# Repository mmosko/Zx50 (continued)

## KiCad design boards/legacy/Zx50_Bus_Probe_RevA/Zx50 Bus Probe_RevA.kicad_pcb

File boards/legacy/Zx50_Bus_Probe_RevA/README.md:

# Zx50 Bus Probe & Injector Card - Hardware Reference

*Note: For details on the firmware (PIC18F4620 and Pi Pico) and the automated laptop testing scripts, please refer to the separate software documentation: [Zx50BusProbeSw.md](../../Zx50_BusProbe_Firmware/Zx50BusProbeSw.md).*

## 1. Overview and Purpose
The Zx50 Bus Probe is a hybrid diagnostic tool designed specifically for a Z80-based Zx50 backplane architecture. It serves as an active oscilloscope probe, an arbitrary signal injector, and a digital logic analyzer tap. 

Instead of manually moving oscilloscope probes across an active backplane, the Zx50 Probe allows a user to digitally route any of the 72 backplane signals to a central BNC output, inject external signals via a BNC input, and monitor system health via an onboard UI.

There is a Receiver card that attaches to the Zx50 bus. It has a Pi PICO as the interface to a host computer. The Pico orchestrates the backplane signal multiplexing. It is attached via SPI to an 18F4620 PIC that has two GPIO expanders. The PIC is the Zx50 bus debugger. It can read or write to the bus and it can control the clocks. 

There is a Sender card that attaches to the Receiver via 2x5 ribbon cable. The Sender card attaches to an AFG to put signals on backplane traces. These can be monitored by the Receiver. Both sender and receiver have high-speed op amps and BNC connectors to attach to lab equipment.

## 2. The Universal Board Architecture
To minimize fabrication costs and guarantee matched signal paths, the system is designed as a **Universal PCB**. A single board design can be populated differently to serve as either the "Receiver" (The Brain) or the "Sender" (The Drone).

* **The Receiver (Master):** Populated with a Raspberry Pi Pico (RP2040) and a PIC18F4620. It orchestrates the signal routing, generates hardware-level system clocks, handles high-speed Z80 interrupts (`~WAIT~`, `~INT~`), and hosts the physical User Interface.
* **The Sender (Slave):** The Pi Pico and PIC are left unpopulated. It relies on the Receiver to command its local analog matrix via a 10-pin right-angle IDC ribbon cable.
* **The Jumper Matrix (3x7 Block):** A physical 21-pin routing block determines the board's role by directing the 5V control signals:
  * **Position 1-2 (Receiver Mode):** The onboard Pico drives both the local analog matrix and the remote Sender board via the ribbon cable.
  * **Position 2-3 (Sender Mode / Mirror Mode):** The local analog matrix is driven by external signals arriving from the ribbon cable.

## 3. Core Subsystems

### A. The "Voltage Firewall" (Level Shifting)
The Pi Pico operates strictly at 3.3V, while the Zx50 backplane and logic operate at 5.0V. 
* A **`74AHCT541`** buffer acts as a unidirectional level shifter and line driver.
* The "T" (TTL-compatible) inputs interpret the Pico's 3.3V signals as a valid logic HIGH, stepping them up to a robust 5.0V to drive the local multiplexers and safely push signals down the ribbon cable to the Sender board.

### B. The Analog Matrix
The core of the probing capability is a massive 72-channel crosspoint matrix.
* **Multiplexers:** Nine `CD74HC4051E` 8-channel analog multiplexers (High-Speed CMOS variant chosen over legacy `CD4051BE` to ensure <70Ω $R_{ON}$ and >100MHz bandwidth for sharp Z80 square waves).
* **Decoding:** A 4-to-16 line decoder (`74HC154` or cascaded `74HC138`s) manages the Chip Select lines for the multiplexers. Sending address `1111` (15) targets a "Phantom Mux," safely disabling the entire matrix to isolate the test equipment from the bus.
* **Op-Amps:** High-speed `OPA356xxD` CMOS operational amplifiers buffer the analog signals immediately before the `IN` and `OUT` BNC jacks to prevent the oscilloscope or function generator from loading the backplane.

### C. The Dedicated Logic Analyzer Field
To support professional diagnostic equipment (e.g., Tektronix logic analyzers), the rear of the card features a raw, unbuffered test point field.
* Arranged in standard 2xN 2.54mm pitch groupings spaced out by function: `ADDR [0:15]`, `DATA [0:7]`, `CTRL [0:7]`, `SHADOW_DATA [0:7]`, `SHADOW_CTRL [0:7]`, and `CLOCK [0:1]`.
* **Dedicated Ground Row:** Every signal pin is paired directly with an adjacent `GND` pin (Row 2), ensuring short return paths and pristine signal integrity for flying-lead probes.
* The headers are intentionally unbuffered, relying on the <2pF capacitance of professional logic analyzer pods to spy on the true analog state of the bus.

## 4. Mechanical & Physical Design

* **Asymmetric "Tower" Form Factor:** The PCB utilizes an inverted-T (or L-shaped) `Edge.Cuts` profile. The base fits the standard 5-inch Zx50 card dimensions, while the front UI section extends upward to 7 inches. This ensures the display and status LEDs clear the adjacent memory/CPU cards in the chassis.
* **User Interface:**
  * **Primary Display:** An `EA DIP205-4` 20x4 Character LCD, mounted flush to the PCB. It runs natively on the Pico's 3.3V SPI bus, with a dedicated 33Ω resistor dropping the 5V rail for the yellow/green backlight.
  * **Status LEDs:** Three right-angle horizontal LEDs (`CLK`, `MCLK`, `PWR`) mounted on the top edge of the board to provide immediate, bench-visible heartbeat and clock status.
* **Horizontal Interconnects:** The PIC ICSP programming header (`J4`) and the Sender/Receiver ribbon cable header (`J8`) use right-angle footprints to prevent cable collisions with adjacent Zx50 cards.

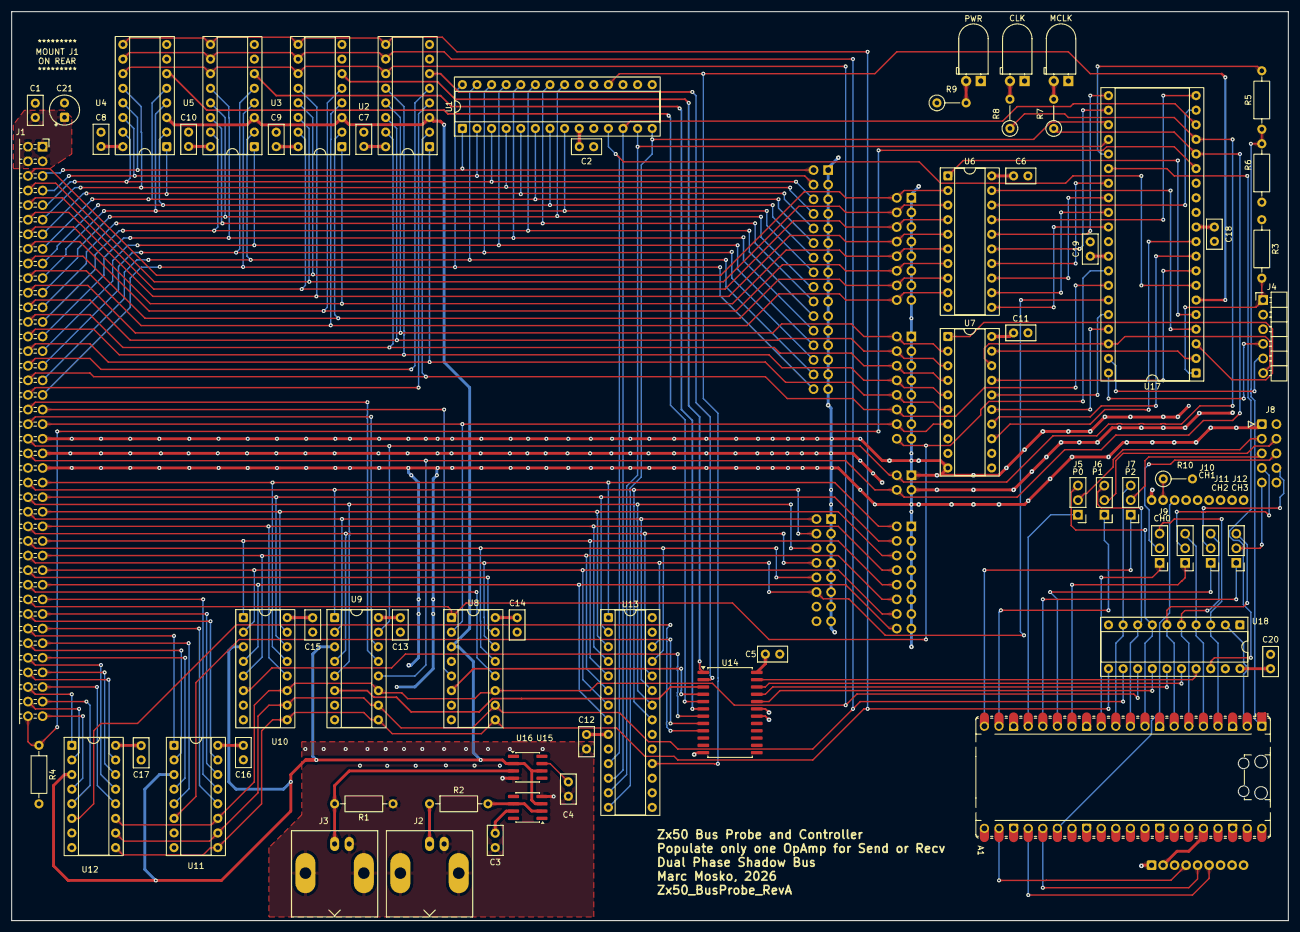
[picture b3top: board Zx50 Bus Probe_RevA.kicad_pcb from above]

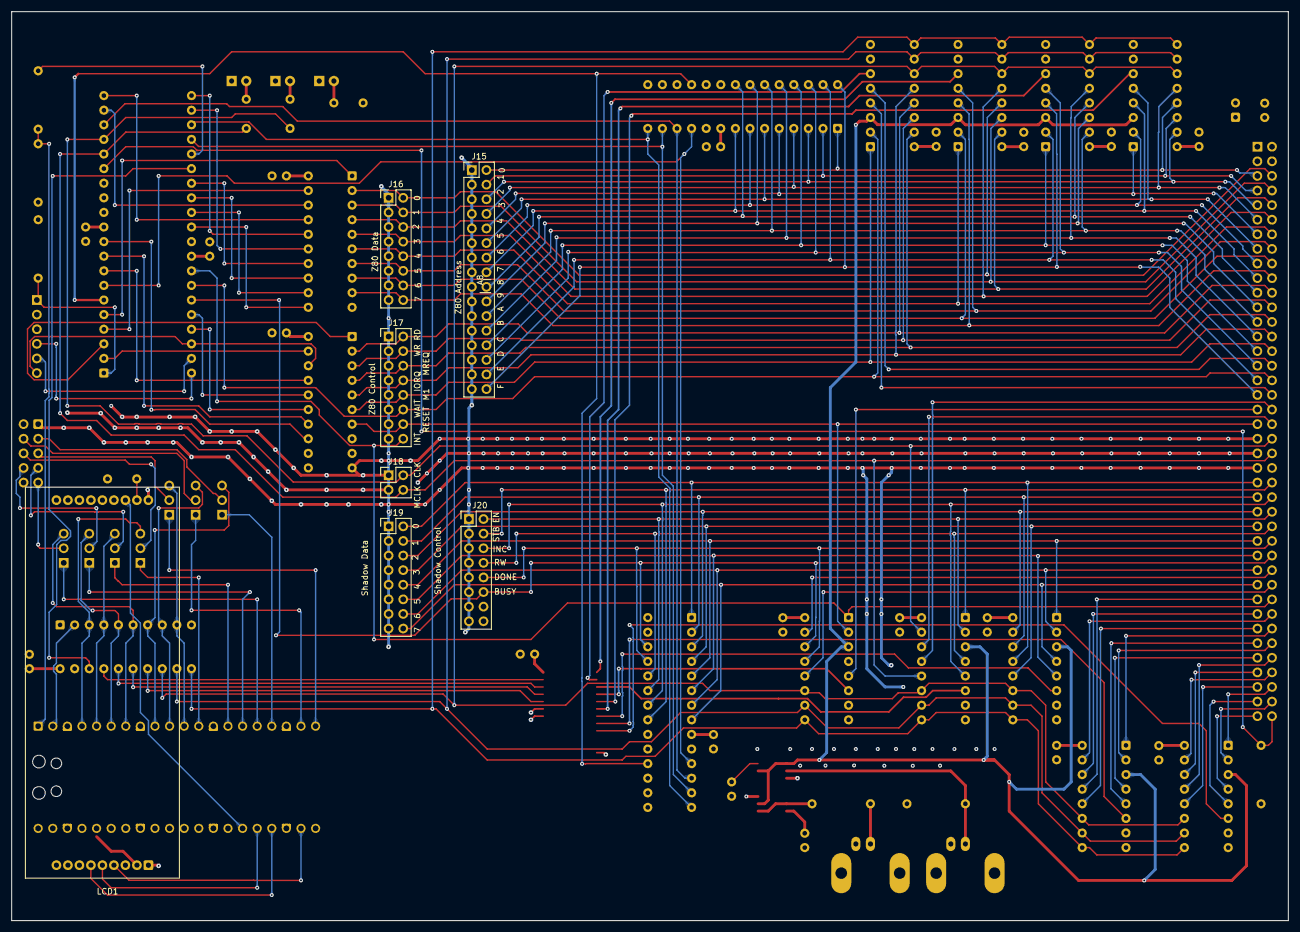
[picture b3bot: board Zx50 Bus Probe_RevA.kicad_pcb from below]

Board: 4 copper layers, 222.1 x 158.1 mm, 72 parts (7 on the bottom side), 154 nets.

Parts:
A1: RaspberryPi_Pico; RaspberryPi_Pico_Common_Unspecified
C1, C2, C3, C4, C5, C6, C7, C8, C9, C10, C11, C12, C13, C14, C15, C16, C17, C18, C19, C20: .1uF; C_Disc_D5.0mm_W2.5mm_P2.50mm
C21: 10uF; CP_Radial_Tantal_D5.0mm_P2.50mm
D1: MCLK; LED_D5.0mm_Horizontal_O1.27mm_Z3.0mm
D2: CLK; LED_D5.0mm_Horizontal_O1.27mm_Z3.0mm
D3: PWR; LED_D5.0mm_Horizontal_O1.27mm_Z3.0mm
J1: Zx50_EdgeConnector; PinSocket_2x40_P2.54mm_Horizontal_Edge
J2: OUT; BNC_Amphenol_B6252HB-NPP3G-50_Horizontal
J3: IN; BNC_Amphenol_B6252HB-NPP3G-50_Horizontal
J4: PIC PGM; PinHeader_1x06_P2.54mm_Horizontal_EDGE
J5: P0; PinHeader_1x03_P2.54mm_Vertical
J6: P1; PinHeader_1x03_P2.54mm_Vertical
J7: P2; PinHeader_1x03_P2.54mm_Vertical
J8: Send/Recv Card; IDC-Header_2x05_P2.54mm_Horizontal_Edge
J9: CH0; PinHeader_1x03_P2.54mm_Vertical
J10: CH1; PinHeader_1x03_P2.54mm_Vertical
J11: CH2; PinHeader_1x03_P2.54mm_Vertical
J12: CH3; PinHeader_1x03_P2.54mm_Vertical
J15: Z80_Addr; PinHeader_2x16_P2.54mm_Vertical_Row_Letter_Last
J16: Z80_Data; PinHeader_2x08_P2.54mm_Vertical_Row_Letter_Last
J17: Z80_Ctrl; PinHeader_2x08_P2.54mm_Vertical_Row_Letter_Last
J18: Clock; PinHeader_2x02_P2.54mm_Vertical_Row_Letter_Last
J19: SH_Data; PinHeader_2x08_P2.54mm_Vertical_Row_Letter_Last
J20: SH_Ctrl; PinHeader_2x08_P2.54mm_Vertical_Row_Letter_Last
LCD1: EA 205G-4NLED; EA_DIG205G-4NLED
R1, R2: 49.9R 1W 1%; R_Axial_DIN0207_L6.3mm_D2.5mm_P10.16mm_Horizontal
R3: 10k; R_Axial_DIN0207_L6.3mm_D2.5mm_P10.16mm_Horizontal
R4: 10K; R_Axial_DIN0207_L6.3mm_D2.5mm_P10.16mm_Horizontal
R5: 2.2k; R_Axial_DIN0207_L6.3mm_D2.5mm_P10.16mm_Horizontal
R6: 3.3k; R_Axial_DIN0207_L6.3mm_D2.5mm_P10.16mm_Horizontal
R7, R8: 2.2K; R_Axial_DIN0207_L6.3mm_D2.5mm_P5.08mm_Vertical
R9: 470; R_Axial_DIN0207_L6.3mm_D2.5mm_P5.08mm_Vertical
R10: 33R; R_Axial_DIN0207_L6.3mm_D2.5mm_P5.08mm_Vertical
U1, U13: MCP23S17_SP; DIP-28_W7.62mm_Socket
U2, U3, U4, U5, U8, U9, U10, U11, U12: CD74HC4051E; DIP-16_W7.62mm_Socket
U6, U7: SN74ABT245BN; DIP-20_W7.62mm_Socket
U14: CD74HC154M96; SOIC-24W_7.5x15.4mm_P1.27mm
U15, U16: OPA356xxD; SOIC-8_3.9x4.9mm_P1.27mm
U17: PIC18F4620-I_P; DIP-40_W15.24mm_Socket
U18: 74AHCT541; DIP-20_W7.62mm_Socket

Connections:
+5V: C1.1, C2.1, C3.1, C4.1, C5.2, C6.1, C7.2, C8.2, C9.2, C10.2, C11.1, C12.1, C13.2, C14.2, C15.2, C16.2, C17.2, C18.1, C19.1, C20.2, C21.1, J1.1 (+5V), J1.2 (+5V), J1.3 (+5V), J1.4 (+5V), J4.2, R3.1, R4.2, R9.1, R10.2, U1.9 (VDD), U2.16 (VCC), U3.16 (VCC), U4.16 (VCC), U5.16 (VCC), U6.20 (VCC), U7.20 (VCC), U8.16 (VCC), U9.16 (VCC), U10.16 (VCC), U11.16 (VCC), U12.16 (VCC), U13.9 (VDD), U13.15 (A0), U14.24 (VCC), U15.7 (V+), U16.7 (V+), U17.11 (VDD), U17.32 (VDD__1), U18.20 (VCC)
/3V3_DISPL: A1.36 (3V3), LCD1.2 (3V3)
/A0: J1.5 (A0), J15.1b, U1.1 (GPB0), U4.13 (A0)
/A1: J1.7 (A1), J15.2b, U1.2 (GPB1), U4.14 (A1)
/A2: J1.9 (A2), J15.3b, U1.3 (GPB2), U4.15 (A2)
/A3: J1.11 (A3), J15.4b, U1.4 (GPB3), U4.12 (A3)
/A4: J1.13 (A4), J15.5b, U1.5 (GPB4), U4.1 (A4)
/A5: J1.15 (A5), J15.6b, U1.6 (GPB5), U4.5 (A5)
/A6: J1.17 (A6), J15.7b, U1.7 (GPB6), U4.2 (A6)
/A7: J1.19 (A7), J15.8b, U1.8 (GPB7), U4.4 (A7)
/A8: J1.21 (A8), J15.9b, U1.21 (GPA0), U5.13 (A0)
/A9: J1.23 (A9), J15.10b, U1.22 (GPA1), U5.14 (A1)
/A10: J1.25 (A10), J15.11b, U1.23 (GPA2), U5.15 (A2)
/A11: J1.27 (A11), J15.12b, U1.24 (GPA3), U5.12 (A3)
/A12: J1.29 (A12), J15.13b, U1.25 (GPA4), U5.1 (A4)
/A13: J1.31 (A13), J15.14b, U1.26 (GPA5), U5.5 (A5)
/A14: J1.33 (A14), J15.15b, U1.27 (GPA6), U5.2 (A6)
/A15: J1.35 (A15), J15.16b, U1.28 (GPA7), U5.4 (A7)
/AN: U2.3 (A), U3.3 (A), U4.3 (A), U5.3 (A), U8.3 (A), U9.3 (A), U10.3 (A), U11.3 (A), U12.3 (A), U15.3 (+), U16.2 (-), U16.6
/AUX: J1.80 (AUX), R4.1, U17.15 (RC0/T1OSO/T13CKI)
/BK_LGT: LCD1.17 (LED_A), R10.1
/CHIP0: U14.23 (A0), U18.17 (Y1)
/CHIP1: U14.22 (A1), U18.16 (Y2)
/CHIP2: U14.21 (A2), U18.15 (Y3)
/CHIP3: U14.20 (A3), U18.14 (Y4)
/CLK: J1.42 (CLK), J18.1b, R8.1, U9.15 (A2), U17.17 (RC2/CCP1/P1A)
/D0: J1.6 (D0), J16.1b, U3.13 (A0), U6.2 (A1)
/D1: J1.8 (D1), J16.2b, U3.14 (A1), U6.3 (A2)
/D2: J1.10 (D2), J16.3b, U3.15 (A2), U6.4 (A3)
/D3: J1.12 (D3), J16.4b, U3.12 (A3), U6.5 (A4)
/D4: J1.14 (D4), J16.5b, U3.1 (A4), U6.6 (A5)
/D5: J1.16 (D5), J16.6b, U3.5 (A5), U6.7 (A6)
/D6: J1.18 (D6), J16.7b, U3.2 (A6), U6.8 (A7)
/D7: J1.20 (D7), J16.8b, U3.4 (A7), U6.9 (A8)
/DISP_CS: A1.22 (GPIO17), LCD1.4 (CS)
/G0: J1.63 (GPIO0), U11.13 (A0)
/G1: J1.65 (GPIO1), U11.14 (A1)
/G2: J1.66 (GPIO2), U11.15 (A2)
/G3: J1.67 (GPIO3), U11.12 (A3)
/G4: J1.68 (GPIO4), U11.1 (A4)
/G5: J1.69 (GPIO5), U11.5 (A5)
/G6: J1.70 (GPIO6), U11.2 (A6)
/G7: J1.71 (GPIO7), U11.4 (A7)
/G8: J1.72 (GPIO8), U12.13 (A0)
/G9: J1.73 (GPIO9), U12.14 (A1)
/G10: J1.74 (GPIO10), U12.15 (A2)
/G11: J1.75 (GPIO11), U12.12 (A3)
/G12: J1.76 (GPIO12), U12.1 (A4)
/G13: J1.77 (GPIO13), U12.5 (A5)
/G14: J1.78 (GPIO14), U12.2 (A6)
/G15: J1.79 (GPIO15), U12.4 (A7)
/IEI: J1.37 (IEI), U8.5 (A5)
/IEO: J1.38 (IEO), U9.13 (A0)
/MCLK: J1.44 (MCLK), J18.2b, R7.1, U9.12 (A3), U17.16 (RC1/T1OSI/CCP2)
/MCLR_N: J4.1, R3.2, U17.1 (~MCLR/VPP/RE3)
/PGC: J4.5, U17.39 (RB6/KBI2/PGC)
/PGD: J4.4, U17.40 (RB7/KBI3/PGD)
/PORT0: U2.11 (S0), U3.11 (S0), U4.11 (S0), U5.11 (S0), U8.11 (S0), U9.11 (S0), U10.11 (S0), U11.11 (S0), U12.11 (S0), U18.13 (Y5)
/PORT1: U2.10 (S1), U3.10 (S1), U4.10 (S1), U5.10 (S1), U8.10 (S1), U9.10 (S1), U10.10 (S1), U11.10 (S1), U12.10 (S1), U18.12 (Y6)
/PORT2: U2.9 (S2), U3.9 (S2), U4.9 (S2), U5.9 (S2), U8.9 (S2), U9.9 (S2), U10.9 (S2), U11.9 (S2), U12.9 (S2), U18.11 (Y7)
/RA0: U7.19 (*OE), U17.2 (RA0/AN0)
/RA1: U7.1 (DIR), U17.3 (RA1/AN1)
/RA2: U6.19 (*OE), U17.4 (RA2/AN2/VREF-/CVREF)
/RA3: U6.1 (DIR), U17.5 (RA3/AN3/VREF+)
/RA4: U1.18 (~RESET), U13.18 (~RESET), U17.6 (RA4/T0CKI/C1OUT)
/RA5: U1.11 (~CS), U13.11 (~CS), U17.7 (RA5/AN4/~SS/HLVDIN/C2OUT)
/RB3: U7.16 (B3), U17.36 (RB3/AN9/CCP2)
/RB4: U7.15 (B4), U17.37 (RB4/KBI0/AN11)
/RB5: J4.6, U7.18 (B1), U17.38 (RB5/KBI1/PGM)
/RD0: U6.18 (B1), U17.19 (RD0/PSP0)
/RD1: U6.17 (B2), U17.20 (RD1/PSP1)
/RD2: U6.16 (B3), U17.21 (RD2/PSP2)
/RD3: U6.15 (B4), U17.22 (RD3/PSP3)
/RD4: U6.14 (B5), U17.27 (RD4/PSP4)
/RD5: U6.13 (B6), U17.28 (RD5/PSP5/P1B)
/RD6: U6.12 (B7), U17.29 (RD6/PSP6/P1C)
/RD7: U6.11 (B8), U17.30 (RD7/PSP7/P1D)
/RE0: U7.17 (B2), U17.8 (RE0/~RD/AN5)
/RE1: U7.14 (B5), U17.9 (RE1/~WR/AN6)
/RE2: U7.13 (B6), U17.10 (RE2/~CS/AN7)
/RX: U17.26 (RC7/RX/DT), U18.18 (Y0)
/SCK: U1.12 (SCK), U13.12 (SCK), U17.18 (RC3/SCK/SCL)
/SD0: J1.47 (SD0), J19.1b, U10.13 (A0), U13.1 (GPB0)
/SD1: J1.49 (SD1), J19.2b, U10.14 (A1), U13.2 (GPB1)
/SD2: J1.51 (SD2), J19.3b, U10.15 (A2), U13.3 (GPB2)
/SD3: J1.53 (SD3), J19.4b, U10.12 (A3), U13.4 (GPB3)
/SD4: J1.55 (SD4), J19.5b, U10.1 (A4), U13.5 (GPB4)
/SD5: J1.57 (SD5), J19.6b, U10.5 (A5), U13.6 (GPB5)
/SD6: J1.59 (SD6), J19.7b, U10.2 (A6), U13.7 (GPB6)
/SD7: J1.61 (SD7), J19.8b, U10.4 (A7), U13.8 (GPB7)
/SDI: U1.14 (SO), U13.14 (SO), U17.23 (RC4/SDI/SDA)
/SDO: U1.13 (SI), U13.13 (SI), U17.24 (RC5/SDO)
/SEL0: U3.6 (~E), U14.1 (S0)
/SEL1: U2.6 (~E), U14.2 (S1)
/SEL2: U9.6 (~E), U14.3 (S2)
/SEL3: U8.6 (~E), U14.4 (S3)
/SEL4: U4.6 (~E), U14.5 (S4)
/SEL5: U5.6 (~E), U14.6 (S5)
/SEL6: U10.6 (~E), U14.7 (S6)
/SEL7: U11.6 (~E), U14.8 (S7)
/SEL8: U12.6 (~E), U14.9 (S8)
/SH_RW: J1.54 (SRW), J20.4b, U9.4 (A7), U13.24 (GPA3)
/SPI_SCK: A1.24 (GPIO18), LCD1.6 (CLK)
/SPI_TX: A1.25 (GPIO19), LCD1.5 (MOSI)
/TX: R5.2, U17.25 (RC6/TX/CK)
/~BUSAK~: J1.62 (~BUSAK~), U8.12 (A3)
/~BUSRQ~: J1.60 (~BUSRQ~), U8.15 (A2)
/~HALT~: J1.40 (~HALT~), U9.14 (A1)
/~INT~: J1.64 (~INT~), J17.8b, U8.1 (A4), U17.33 (RB0/INT0/FLT0/AN12)
/~IORQ~: J1.28 (~IORQ~), J17.4b, U2.12 (A3), U7.5 (A4)
/~M1~: J1.30 (~M1~), J17.5b, U2.1 (A4), U7.6 (A5)
/~MREQ~: J1.26 (~MREQ~), J17.3b, U2.15 (A2), U7.4 (A3)
/~NMI~: J1.36 (~NMI~), U2.4 (A7)
/~RD~: J1.22 (~RD~), J17.1b, U2.13 (A0), U7.2 (A1)
/~RESET~: J1.39 (~RESET~), J17.7b, U7.7 (A6), U8.2 (A6)
/~RFSH~: J1.32 (~RFSH~), U2.5 (A5)
/~SH_BUSY~: J1.58 (~S_BUSY~), J20.6b, U8.14 (A1), U13.26 (GPA5), U17.35 (RB2/INT2/AN8)
/~SH_DONE~: J1.56 (~S_DONE~), J20.5b, U8.13 (A0), U13.25 (GPA4)
/~SH_EN~: J1.52 (~S_EN~), J20.1b, U9.2 (A6), U13.23 (GPA2)
/~SH_INC~: J1.50 (~SINC~), J20.3b, U9.5 (A5), U13.22 (GPA1)
/~SH_STB~: J1.48 (~SSTB~), J20.2b, U9.1 (A4), U13.21 (GPA0)
/~WAIT~: J1.34 (~WAIT~), J17.6b, U2.2 (A6), U17.34 (RB1/INT1/AN10)
/~WR~: J1.24 (~WR~), J17.2b, U2.14 (A1), U7.3 (A2)
GND: A1.3 (GND), A1.8 (GND), A1.13 (GND), A1.18 (GND), A1.23 (GND), A1.28 (GND), A1.38 (GND), C1.2, C2.2, C3.2, C4.2, C5.1, C6.2, C7.1, C8.1, C9.1, C10.1, C11.2, C12.2, C13.1, C14.1, C15.1, C16.1, C17.1, C18.2, C19.2, C20.1, C21.2, D1.1 (K), D2.1 (K), D3.1 (K), J1.41 (GND), J1.43 (GND), J1.45 (GND), J1.46 (GND), J2.2 (Ext), J3.2 (Ext), J4.3, J8.1, J8.2, J8.10, J15.1a, J15.2a, J15.3a, J15.4a, J15.5a, J15.6a, J15.7a, J15.8a, J15.9a, J15.10a, J15.11a, J15.12a, J15.13a, J15.14a, J15.15a, J15.16a, J16.1a, J16.2a, J16.3a, J16.4a, J16.5a, J16.6a, J16.7a, J16.8a, J17.1a, J17.2a, J17.3a, J17.4a, J17.5a, J17.6a, J17.7a, J17.8a, J18.1a, J18.2a, J19.1a, J19.2a, J19.3a, J19.4a, J19.5a, J19.6a, J19.7a, J19.8a, J20.1a, J20.2a, J20.3a, J20.4a, J20.5a, J20.6a, J20.7a, J20.8a, LCD1.1 (GND), LCD1.18 (LED_C), R1.1, R6.1, U1.10 (VSS), U1.15 (A0), U1.16 (A1), U1.17 (A2), U2.7 (VEE), U2.8 (GND), U3.7 (VEE), U3.8 (GND), U4.7 (VEE), U4.8 (GND), U5.7 (VEE), U5.8 (GND), U6.10 (GND), U7.10 (GND), U8.7 (VEE), U8.8 (GND), U9.7 (VEE), U9.8 (GND), U10.7 (VEE), U10.8 (GND), U11.7 (VEE), U11.8 (GND), U12.7 (VEE), U12.8 (GND), U13.10 (VSS), U13.16 (A1), U13.17 (A2), U14.12 (GND), U14.18 (E0), U14.19 (E1), U15.4 (V-), U16.4 (V-), U17.12 (VSS), U17.31 (VSS__1), U18.1 (G1), U18.10 (GND), U18.19 (G2)
unnamed: A1.1 (GPIO0), R5.1, R6.2
unnamed: A1.2 (GPIO1), U18.2 (A0)
unnamed: A1.4 (GPIO2), J9.3, U18.3 (A1)
unnamed: A1.5 (GPIO3), J10.3, U18.4 (A2)
unnamed: A1.6 (GPIO4), J11.3, U18.5 (A3)
unnamed: A1.7 (GPIO5), J12.3, U18.6 (A4)
unnamed: A1.9 (GPIO6), J5.3, U18.7 (A5)
unnamed: A1.10 (GPIO7), J6.3, U18.8 (A6)
unnamed: A1.11 (GPIO8), J7.3, U18.9 (A7)
unnamed: A1.12 (GPIO9), J9.1
unnamed: A1.14 (GPIO10), J10.1
unnamed: A1.15 (GPIO11), J11.1
unnamed: A1.16 (GPIO12), J12.1
unnamed: A1.17 (GPIO13), J5.1
unnamed: A1.19 (GPIO14), J6.1
unnamed: A1.20 (GPIO15), J7.1
unnamed: A1.26 (GPIO20), LCD1.16 (RST)
unnamed: D1.2 (A), R7.2
unnamed: D2.2 (A), R8.2
unnamed: D3.2 (A), R9.2
unnamed: J2.1 (In), R2.1
unnamed: J3.1 (In), R1.2, U16.3 (+)
unnamed: J5.2, J8.3
unnamed: J6.2, J8.4
unnamed: J7.2, J8.5
unnamed: J8.6, J9.2
unnamed: J8.7, J10.2
unnamed: J8.8, J11.2
unnamed: J8.9, J12.2
unnamed: R2.2, U15.2 (-), U15.6

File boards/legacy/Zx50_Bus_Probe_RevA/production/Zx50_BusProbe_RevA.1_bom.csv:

Designator,Footprint,Quantity,Value,LCSC Part #
A1,RaspberryPi_Pico_Common_Unspecified,1,RaspberryPi_Pico,
"C1, C10, C11, C12, C13, C14, C15, C16, C17, C18, C19, C2, C20, C3, C4, C5, C6, C7, C8, C9",C_Disc_D5.0mm_W2.5mm_P2.50mm,20,.1uF,
C21,CP_Radial_Tantal_D5.0mm_P2.50mm,1,10uF,
D1,LED_D5.0mm_Horizontal_O1.27mm_Z3.0mm,1,MCLK,
D2,LED_D5.0mm_Horizontal_O1.27mm_Z3.0mm,1,CLK,
D3,LED_D5.0mm_Horizontal_O1.27mm_Z3.0mm,1,PWR,
J1,PinSocket_2x40_P2.54mm_Horizontal_Edge,1,Zx50_EdgeConnector,
J10,PinHeader_1x03_P2.54mm_Vertical,1,CH1,
J11,PinHeader_1x03_P2.54mm_Vertical,1,CH2,
J12,PinHeader_1x03_P2.54mm_Vertical,1,CH3,
J15,PinHeader_2x16_P2.54mm_Vertical_Row_Letter_Last,1,Z80_Addr,
J16,PinHeader_2x08_P2.54mm_Vertical_Row_Letter_Last,1,Z80_Data,
J17,PinHeader_2x08_P2.54mm_Vertical_Row_Letter_Last,1,Z80_Ctrl,
J18,PinHeader_2x02_P2.54mm_Vertical_Row_Letter_Last,1,Clock,
J19,PinHeader_2x08_P2.54mm_Vertical_Row_Letter_Last,1,SH_Data,
J2,BNC_Amphenol_B6252HB-NPP3G-50_Horizontal,1,OUT,
J20,PinHeader_2x08_P2.54mm_Vertical_Row_Letter_Last,1,SH_Ctrl,
J3,BNC_Amphenol_B6252HB-NPP3G-50_Horizontal,1,IN,
J4,PinHeader_1x06_P2.54mm_Horizontal_EDGE,1,PIC PGM,
J5,PinHeader_1x03_P2.54mm_Vertical,1,P0,
J6,PinHeader_1x03_P2.54mm_Vertical,1,P1,
J7,PinHeader_1x03_P2.54mm_Vertical,1,P2,
J8,IDC-Header_2x05_P2.54mm_Horizontal_Edge,1,Send/Recv Card,
J9,PinHeader_1x03_P2.54mm_Vertical,1,CH0,
LCD1,EA_DIG205G-4NLED,1,EA 205G-4NLED,
"R1, R2",R_Axial_DIN0207_L6.3mm_D2.5mm_P10.16mm_Horizontal,2,49.9R 1W 1%,
R10,R_Axial_DIN0207_L6.3mm_D2.5mm_P5.08mm_Vertical,1,33R,
"R3, R4",R_Axial_DIN0207_L6.3mm_D2.5mm_P10.16mm_Horizontal,2,10k,
R5,R_Axial_DIN0207_L6.3mm_D2.5mm_P10.16mm_Horizontal,1,2.2k,
R6,R_Axial_DIN0207_L6.3mm_D2.5mm_P10.16mm_Horizontal,1,3.3k,
"R7, R8",R_Axial_DIN0207_L6.3mm_D2.5mm_P5.08mm_Vertical,2,2.2K,
R9,R_Axial_DIN0207_L6.3mm_D2.5mm_P5.08mm_Vertical,1,470,
"U1, U13",DIP-28_W7.62mm_Socket,2,MCP23S17_SP,
"U10, U11, U12, U2, U3, U4, U5, U8, U9",DIP-16_W7.62mm_Socket,9,CD74HC4051E,
U14,SOIC-24W_7.5x15.4mm_P1.27mm,1,CD74HC154M96,
"U15, U16",SOIC-8_3.9x4.9mm_P1.27mm,2,OPA356xxD,
U17,DIP-40_W15.24mm_Socket,1,PIC18F4620-I_P,
U18,DIP-20_W7.62mm_Socket,1,74AHCT541,
"U6, U7",DIP-20_W7.62mm_Socket,2,SN74ABT245BN,

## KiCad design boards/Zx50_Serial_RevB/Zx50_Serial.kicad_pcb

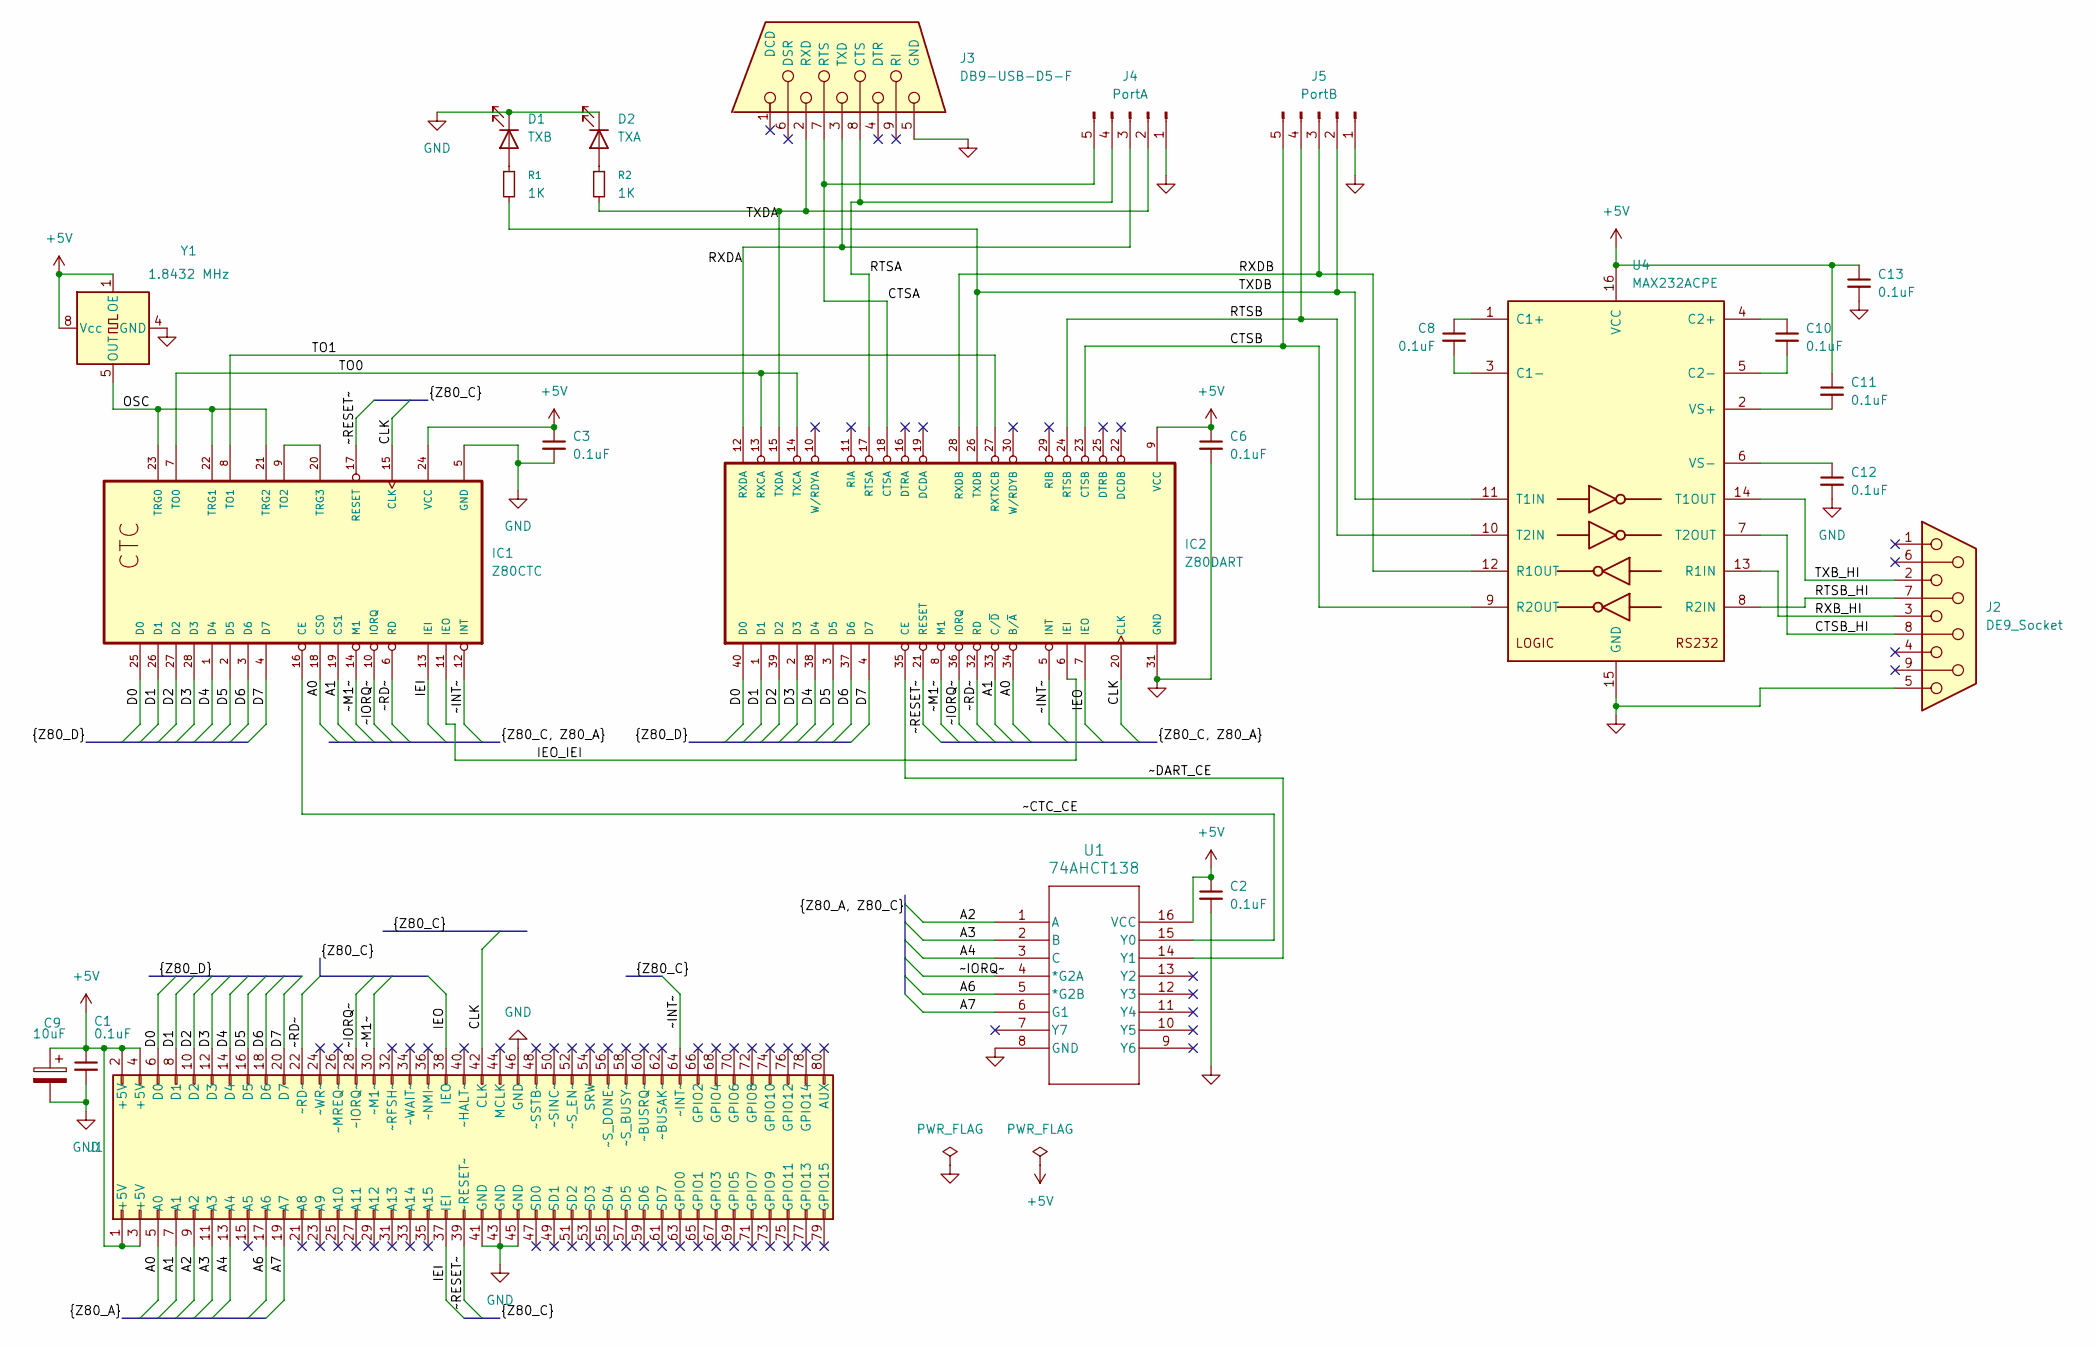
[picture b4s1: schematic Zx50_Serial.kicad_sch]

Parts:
C1, C2, C3, C6, C8, C10, C11, C12, C13: 0.1uF; C_Disc_D5.0mm_W2.5mm_P5.00mm; DigiKey_PN BC1101CT-ND
C9: 10uF; CP_Radial_Tantal_D5.0mm_P2.50mm; DigiKey_PN 399-1418-ND
D1: TXB; LED_D5.0mm
D2: TXA; LED_D5.0mm
IC1: Z80CTC; DIP-28_W15.24mm_Socket
IC2: Z80DART; DIP-40_W15.24mm_Socket
J1: Zx50_EdgeConnector; PinSocket_2x40_P2.54mm_Vertical_Oval; DigiKey_PN A34273-40-ND
J2: DE9_Socket; DSUB-9_Receptical_A-DF_09_A_KG-T2S
J3: DB9-USB-D5-F; DSUB-9_Receptical_A-DF_09_A_KG-T2S; DigiKey_PN 768-1108-ND
J4: PortA; PinHeader_1x05_P2.54mm_Horizontal
J5: PortB; PinHeader_1x05_P2.54mm_Horizontal
R1, R2: 1K; R_Axial_DIN0207_L6.3mm_D2.5mm_P10.16mm_Horizontal
U1: 74AHCT138; DIP-16_W7.62mm_Socket; DigiKey_PN 296-4666-5-ND
U4: MAX232ACPE; DIP-16_W7.62mm_Socket; DigiKey_PN MAX232ACPE+-ND
Y1: 1.8432 MHz; Oscillator_DIP-8; Mouser_PN 520-TCH184-X

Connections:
+5V: C1.1, C2.1, C3.1, C6.1, C9.1, C11.1, C13.1, IC1.24 (VCC), IC2.9 (VCC), J1.1 (+5V), J1.2 (+5V), J1.3 (+5V), J1.4 (+5V), U1.16 (VCC), U4.16 (VCC), Y1.1 (OE), Y1.8 (Vcc); also elsewhere on the board
/A0: IC1.18 (CS0), IC2.34 (B/~A), J1.5 (A0)
/A1: IC1.19 (CS1), IC2.33 (C/~D), J1.7 (A1)
/A2: J1.9 (A2), U1.1 (A)
/A3: J1.11 (A3), U1.2 (B)
/A4: J1.13 (A4), U1.3 (C)
/A6: J1.17 (A6), U1.5 (*G2B)
/A7: J1.19 (A7), U1.6 (G1)
/CLK: IC1.15 (CLK), IC2.20 (CLK), J1.42 (CLK)
/CTSA: IC2.18 (CTSA), J3.7 (RTS), J4.5
/CTSB: IC2.23 (CTSB), J5.5, U4.9 (R2OUT)
/CTSB_HI: J2.8, U4.7 (T2OUT)
/D0: IC1.25 (D0), IC2.40 (D0), J1.6 (D0)
/D1: IC1.26 (D1), IC2.1 (D1), J1.8 (D1)
/D2: IC1.27 (D2), IC2.39 (D2), J1.10 (D2)
/D3: IC1.28 (D3), IC2.2 (D3), J1.12 (D3)
/D4: IC1.1 (D4), IC2.38 (D4), J1.14 (D4)
/D5: IC1.2 (D5), IC2.3 (D5), J1.16 (D5)
/D6: IC1.3 (D6), IC2.37 (D6), J1.18 (D6)
/D7: IC1.4 (D7), IC2.4 (D7), J1.20 (D7)
/IEI: IC1.13 (IEI), J1.37 (IEI)
/IEO: IC2.7 (IEO), J1.38 (IEO)
/IEO_IEI: IC1.11 (IEO), IC2.6 (IEI)
/OSC: IC1.21 (TRG2), IC1.22 (TRG1), IC1.23 (TRG0), Y1.5 (OUT)
/RTSA: IC2.17 (RTSA), J3.8 (CTS), J4.4
/RTSB: IC2.24 (RTSB), J5.4, U4.10 (T2IN)
/RTSB_HI: J2.7, U4.8 (R2IN)
/RXB_HI: J2.3, U4.13 (R1IN)
/RXDA: IC2.12 (RXDA), J3.3 (TXD), J4.3
/RXDB: IC2.28 (RXDB), J5.3, U4.12 (R1OUT)
/TO0: IC1.7 (TO0), IC2.13 (RXCA), IC2.14 (TXCA)
/TO1: IC1.8 (TO1), IC2.27 (RXTXCB)
/TXB_HI: J2.2, U4.14 (T1OUT)
/TXDA: IC2.15 (TXDA), J3.2 (RXD), J4.2, R2.2
/TXDB: IC2.26 (TXDB), J5.2, R1.2, U4.11 (T1IN)
/~CTC_CE: IC1.16 (CE), U1.15 (Y0)
/~DART_CE: IC2.35 (CE), U1.14 (Y1)
/~INT~: IC1.12 (INT), IC2.5 (INT), J1.64 (~INT~)
/~IORQ~: IC1.10 (IORQ), IC2.36 (IORQ), J1.28 (~IORQ~), U1.4 (*G2A)
/~M1~: IC1.14 (M1), IC2.8 (M1), J1.30 (~M1~)
/~RD~: IC1.6 (RD), IC2.32 (RD), J1.22 (~RD~)
/~RESET~: IC1.17 (RESET), IC2.21 (RESET), J1.39 (~RESET~)
GND: C1.2, C2.2, C3.2, C6.2, C9.2, C12.2, C13.2, D1.1 (K), D2.1 (K), IC1.5 (GND), IC2.31 (GND), J1.41 (GND), J1.43 (GND), J1.45 (GND), J1.46 (GND), J2.5, J3.5 (GND), J4.1, J5.1, U1.8 (GND), U4.15 (GND), Y1.4 (GND); also elsewhere on the board
unnamed: D1.2 (A), R1.1
unnamed: D2.2 (A), R2.1
unnamed: IC1.9 (TO2), IC1.20 (TRG3)
unnamed: C8.1, U4.1 (C1+)
unnamed: C8.2, U4.3 (C1-)
unnamed: C10.1, U4.4 (C2+)
unnamed: C10.2, U4.5 (C2-)
unnamed: C11.2, U4.2 (VS+)
unnamed: C12.1, U4.6 (VS-)

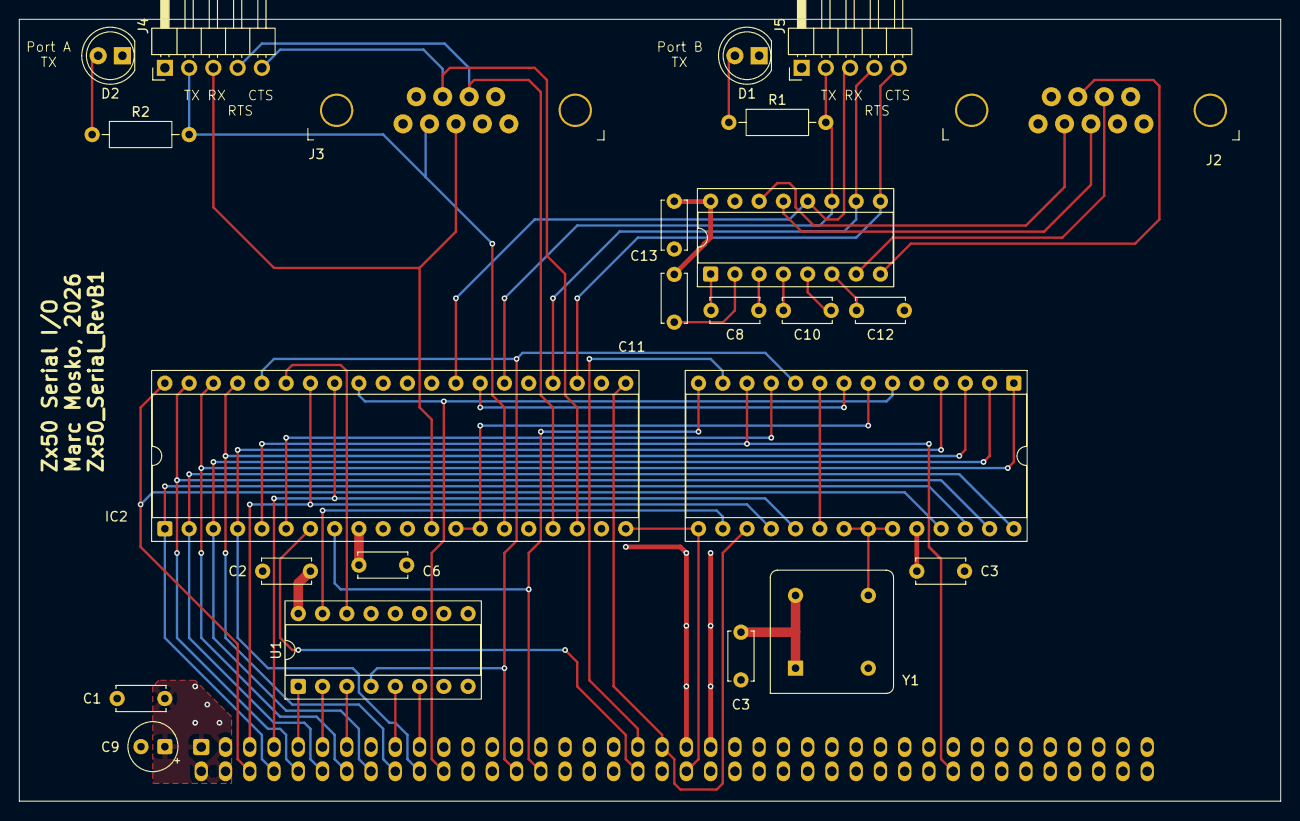
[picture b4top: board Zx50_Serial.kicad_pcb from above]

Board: 4 copper layers, 132.1 x 81.9 mm, 25 parts (1 on the bottom side), 52 nets.

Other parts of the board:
C3#2: 0.1uF; C_Disc_D5.0mm_W2.5mm_P5.00mm

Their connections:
+5V: C3#2.1; also elsewhere on the board
GND: C3#2.2; also elsewhere on the board

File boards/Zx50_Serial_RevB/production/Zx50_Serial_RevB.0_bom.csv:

Designator,Footprint,Quantity,Value,LCSC Part #
"C1, C10, C11, C12, C13, C2, C3_2, C3, C6, C8",C_Disc_D5.0mm_W2.5mm_P5.00mm,10,0.1uF,
C9,CP_Radial_Tantal_D5.0mm_P2.50mm,1,10uF,
D1,LED_D5.0mm,1,TXB,
D2,LED_D5.0mm,1,TXA,
IC1,DIP-28_W15.24mm_Socket,1,Z80CTC,
IC2,DIP-40_W15.24mm_Socket,1,Z80DART,
J1,PinSocket_2x40_P2.54mm_Vertical_Oval,1,Zx50_EdgeConnector,
J2,DSUB-9_Receptical_A-DF_09_A_KG-T2S,1,DE9_Socket,
J3,DSUB-9_Receptical_A-DF_09_A_KG-T2S,1,DB9-USB-D5-F,
J4,PinHeader_1x05_P2.54mm_Horizontal,1,PortA,
J5,PinHeader_1x05_P2.54mm_Horizontal,1,PortB,
"R1, R2",R_Axial_DIN0207_L6.3mm_D2.5mm_P10.16mm_Horizontal,2,1K,
U1,DIP-16_W7.62mm_Socket,1,74AHCT138,
U4,DIP-16_W7.62mm_Socket,1,MAX232ACPE,
Y1,Oscillator_DIP-8,1,7.3728 MHz,

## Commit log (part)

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2026-03-01 Zx50 Bus
2026-03-01 update README and add .gitignore file
2026-03-02 first draft of distributed MMU and testbench.
2026-03-03 Lots of work defining the MMU and now the bus arbiter.
2026-03-03 refactored code for card layout. changed to make all for CI.
2026-03-04 Cleanup before cpld synth
2026-03-05 cleanup card bus names and finish off tests.
2026-03-06 Implement shadow bus protocol. Not tested yet.
2026-03-06 first dma test passes.
2026-03-06 verified concurent access with 3 cards.
2026-03-07 some bus renaming, and better timing tests.
2026-03-09 First PCBA submission
2026-03-09 add missing files
2026-03-13 Documentation update
2026-03-14 added clock mezzanine model
2026-03-14 Add cpu card start and missing files.
2026-03-14 final cpu schematic before pcb layout
2026-03-14 add ground plane
2026-03-14 4 layer done
2026-03-16 serial card
2026-03-16 start towards synthesis
2026-03-17 updates for yosys synthesis
2026-03-17 begin refactor for synthesis updates.
2026-03-17 Refactor before combining projects
2026-03-17 reorg before repo merge
2026-03-17 updates for atl1508_yosys
2026-03-17 updates to fix yosys errors
2026-03-17 update makefile for improved path handling.
2026-03-17 remote nested ternary branches
2026-03-17 save pins
2026-03-17 add syn as phony
2026-03-17 updates before brain surgery to reduce pin count
2026-03-17 split off dma code to make it fit in cpld.
2026-03-17 working around yosys and fitter issues
2026-03-17 fixed copy paste error
2026-03-17 updates to get SVF generated
2026-03-17 update docs
2026-03-18 hacks to reduce cell sizes
2026-03-18 notes on new chips
2026-03-18 fix dma for 4 bits masked out
2026-03-18 get rid of pal_bits and use a decoder.
2026-03-18 fix wiring loop, do not use an output in wiring logic.
2026-03-18 more hacks to reduce complexity
2026-03-18 put the boot initialization back
2026-03-18 more wire cleanup
2026-03-20 add output files
2026-03-20 emergency fixes for miswired memory
2026-03-20 revised based on recent board updates
2026-03-20 update synthesis
2026-03-20 hacks around the a[11] fiasco
2026-03-21 rewrite it all to get clean tests and hardware with DMA and ROM.
2026-03-21 optimize dma adder
2026-03-21 optmize dma adder
2026-03-21 fitted with quartus
2026-03-21 updates to make it fit in 128 cells.
2026-03-21 a11 bug fix now working
2026-03-21 fit the A11 bug fix
2026-03-21 fixup unit tests
2026-03-22 MPLAB project for bus probe 18F4620
2026-03-22 Add firmware for the bus probe
2026-03-22 Reorg bus probe code for pycharm rather than vscode.
2026-03-22 Add some fake data to test the analysis notebook.
2026-03-22 move docs to a central place
2026-03-22 Reorg the pycharm project again. update documentation with current status and software progress.
2026-03-25 add faceplate and display card
2026-03-25 more work on front panels and start to front panel firmware
2026-03-25 reorg documentation.
2026-03-25 Remove old front panel docs and use new version.
2026-03-26 working on firmware, now have a real pico to play with.
2026-03-26 updates to busprobe firmware.
2026-03-27 lots of hacking to get bus probe running.
2026-03-27 enable wifi support for the bus probe
2026-03-28 top level project
2026-03-28 Add extra banners and such to tcp server. updates to revb bus probe.
2026-03-28 updates for more robust tcp handing.
2026-03-28 ignore idea
2026-03-28 re-add serial connections
2026-03-28 fix bug in send_pico_cmd
2026-03-28 Split usb and wifi into different implementations.
2026-03-29 fix syntax for pico commands.
2026-03-29 Add ore connection debugging
2026-03-29 try to get tektronix to interface
2026-03-30 Got the scope working reliably.
2026-03-30 beef up pico wifi on disconnect handling. Remove .idea directories.
2026-04-08 Many updates and board revisions.
    - Backplane Rev D for better AC termination.
    - BusProbe revision, much smaller card, use surface mount, faster multiplexers.
    - Revised clock mezzanine to reduce ringing.
2026-04-08 add script to program atf1509
2026-04-09 update makefile with flash commands that work
2026-04-10 updates to try and make fit without losing pins
2026-04-10 remove bad yosys synthesis. use quartus
2026-04-10 add command to program atf1508
2026-04-10 make scripts x and not sudo
2026-04-11 rewrite cpld code in more structured Amaranth state machine.
2026-04-13 amaranth was a bust, but got a state machine out of it and moving back to verilog with model_rev1.
2026-04-21 update some docs
2026-04-22 add bus arbiter back in. Add DMA back in. Fully tested.
2026-04-22 remove python HDL attempt
2026-04-22 add depenencies back to DMA_SRC
2026-04-25 update mem control to remove boot_en_n logic to save a pin.
2026-04-25 remove the boot_en logic from tests.
2026-04-25 try to simplify logic to reduce cell count
2026-04-25 tell fitter to keep some nets to avoid high fan out
2026-04-25 split responding to intack wire
2026-04-25 update some tests that used wrong exit function
2026-04-29 final hacks for fitter and output from quartus.
2026-04-29 revb memory board,
2026-04-29 add in lost annotation.
2026-04-30 tweeks before refitting with quartus
2026-04-30 try some simplifications for page_ownership
2026-04-30 more hacks for fitter, getting close.
2026-04-30 reduce card id to 2 bits
2026-05-01 reduce card_addr to 2 bits
2026-05-01 simplify the page_ownership by always using same A bits.
2026-05-01 finally got things to fit and generated new CPLD firmware.
2026-05-01 more work on revb memory card, plus a diag program for rev a1.
2026-05-02 add a free-running mclk/zclk to PIC, can now do queued commands that do bus operations on ZCLK T cycles.
2026-05-02 updates to diag verilog
2026-05-02 reorg memory card firmware. create an mmu only version without dma for testing.
2026-05-02 fix CLI bug
2026-05-03 clean up some test benches
2026-05-03 update quartus project
2026-05-04 fixup pic z80 timing. add memory test script to pico
2026-05-04 more reliable pico-pic serial comms
2026-05-04 more z80 bus tests to memory card
2026-05-12 Lots of updates: Work on memory card Rev C with Lattice XO3LF, finish up the front panel card firmware for the pico., add some results for the clock mezzanine Rev B.
2026-05-16 work on rev c1 with lattice lcmxo3lf
2026-05-16 fix filename
2026-05-16 add missing file
2026-05-16 switch to card 1 not 3
2026-05-16 board updates, front panel firmware updates, pic upates for booting
2026-05-17 begin work on async pico-pic protocol, switching to feature branch
2026-05-17 async firmware ready.
2026-05-17 debounce releasing step and provide way to clear pico state machine
2026-05-21 pico async is ok, merge to master. Also add recent work on hw boards
2026-05-28 reorg firmware
2026-05-30 refactor bus probe firmware for Rev B board
2026-06-23 fixes for pic uart overflow
2026-06-28 fireware fixes for serial card and getting pico-pic async working better.
2026-06-28 version 1 of zx50 monitor.
2026-06-29 updates for better memory map, getting ready for xmodem program load.
2026-06-30 code reord, xmodem upload working. checksum verify working.
2026-06-30 enable IM2 interrupts. clock interrupt 0x06 now firing.
